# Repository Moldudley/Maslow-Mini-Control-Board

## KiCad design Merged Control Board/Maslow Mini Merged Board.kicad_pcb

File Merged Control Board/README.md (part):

# Maslow Mini — Merged Control Board

A third KiCad project that puts both existing boards on one PCB:

| Source | What it is | Files |
|---|---|---|
| `../Motor Controller Board/` | "Four Motor Control Board M5" — ESP32-S3, 4× DRV8876 belt-axis drivers, TCA9546A I²C mux, SD NAND, LM2596 3.3 V buck, XT60 inlet | **PCB only, no schematic** |
| `../KiCad Boards/` | "Driver Board 2026-08-01" — ESP32-S3, 2× MP6541A 3-phase drivers, MP2459 3.3 V buck, beam-break homing, vacuum control | schematic + PCB |

**Scope: schematic, plus a partially-placed PCB.** The mechanically-constrained parts are placed;
the rest are staged off-board for manual placement. Nothing is routed yet.

The merge is in two parts: joining the two circuits, and then removing the redundancy that a
single board makes pointless. **169 parts / 61 BOM lines → 156 parts / 53 BOM lines.**

## The design decision you asked for

Both ESP32-S3 MCUs are retained. They are wired to each other **only** on the BoardCom pair,
which is exactly what the mated `H1` 2×5 headers used to carry:

| Merged net | Motor section | Driver section |
|---|---|---|
| `BOARDCOM_A` | `U110` pin 9 — IO16 | `U12` pin 31 — IO38 |
| `BOARDCOM_B` | `U110` pin 8 — IO15 | `U12` pin 32 — IO39 |

Note the crossover. On the original boards both headers carried a net called `BOARDCOM1` on
pins 1/3 and `BOARDCOM2` on pins 2/4 — but with the *opposite* assignment on each board, so
mating them swapped the pair. That swap is preserved here.

`H1` is deleted from both sections. Its remaining pins were power, so:

* pins 6/8/10 (`VIN` on the driver, `VCC` on the motor board) become **one shared `VIN` rail**
* pins 5/7/9 become **one shared `GND`**

## What was consolidated

Once both circuits sit on one board, some parts are doing the same job twice.

### One 3.3 V regulator

The driver board's `U2` was an **MP2459 — 0.5 A**, feeding an ESP32-S3-WROOM-1 that peaks around
355 mA on WiFi transmit. That rail had almost no margin before the merge. The motor board's
`U116` is an **LM2596-3.3 — 3 A**. Combined 3.3 V load across both sections is roughly 530 mA
typical, ~950 mA worst case, so the LM2596 carries both with ~3× headroom.

Deleted: `U2`, `L3` (47 µH), `D2` (catch), `D6` (OR-ing), `C80`, `C81`, `R61`, `R62`, `R63`.
`D7` is kept and now ORs the driver USB port's VBUS into the shared `VIN_BUCK`, so either USB
port can still power the whole board. `+3V3_MC` and `+3V3_DRV` are gone; there is one `+3V3`.

### One reset

The motor MCU had no reset button at all — just an RC on `EN`. Both `EN` pins now share one net
(`RST`) driven by `SW2`, with `R28` (10 kΩ) and `C134` (1 µF) as the single RC. `R128` and `C30`
are deleted. The 1 µF is kept over the driver board's 100 nF because that is the value
Espressif's design guide asks for.

### One power-on LED, one Schottky part number

`D101` + `R115` deleted; the driver section's `LED2` + `R17` is kept (3.6 mA rather than 11 mA,
and the LED was explicitly specified for low forward voltage on a 3.3 V rail). `D102`/`D103`
change from SS14 (40 V / 1 A) to the SS36 (60 V / 3 A) already used by `D7` — one BOM line
instead of two, and more margin on a 24 V rail that also carries six motor stages.

### Summary

| | parts | BOM lines |
|---|---|---|
| MP2459 buck chain | 9 | 6 |
| second power-on LED | 2 | 1 |
| second EN RC | 2 | 0 |
| SS14 → SS36 | 0 | 1 |
| **total** | **13** | **8** |

Nothing was added.

## What stays separate

Each section keeps its own ESP32-S3, its own USB-C programming port and its own boot button
(`BOOT_MC` / `BOOT_DRV`). Combining the two MCUs was explicitly out of scope. Combining the two
USB ports would need a hub IC — a net part *increase* — or flashing the driver MCU through the
motor MCU, which costs firmware work and makes recovery from a bad flash harder.

Also deliberately untouched: the VIN bulk capacitance. `C140` (680 µF) and `C72`/`C73`
(2× 220 µF) were sized as two independent reservoirs because a header sat between them, and one
of the 220 µF is probably surplus now — but that is a ripple-current question, not a schematic
one. The ten 1 kΩ I2C pull-ups are also unchanged; each mux channel needs its own pair, though
1 kΩ is unusually strong (2.2–4.7 kΩ is conventional).

## Two consequences of running one regulator

1. **USB-only power is tighter.** Each buck used to have its own port's 500 mA. Now both MCUs
   run from whichever single port is plugged in — fine for flashing (~230 mA from 5 V), close to
   the limit with both radios live (~460 mA). Plugging in both ports does not help; the diode-OR
   takes only the higher one.
2. **Dropout on USB power.** The LM2596 needs roughly Vout + 1.5–2 V. 5 V minus cable sag minus
   the OR-ing diode leaves ~4.3 V at high load. Fine at flashing currents, marginal at full load.
   This already existed on the motor board; merging just makes more depend on it.

## Naming

| Original | Merged | Why |
|---|---|---|
| motor `VCC` | `VIN` | merges with the driver rail H1 used to carry |
| motor `3V3`, driver `3V3` | `+3V3` | one regulator now, so one rail |
| motor `MCU_RST`, driver `RST` | `RST` | one reset for both MCUs |
| motor `U16_1`, driver `VIN_BUCK` | `VIN_BUCK` | one buck input, fed by three OR-ing diodes |
| motor `BOOT` | `BOOT_MC` | each MCU keeps its own boot button |
| driver `BOOT` | `BOOT_DRV` | " |
| motor `L2_1`, `U2_6`… | `SW_BUCK`, `IPROPI_TR`… | the source PCB had auto-generated net names |

Motor-section reference designators are **the originals + 100** (`U2`→`U102`, `C7`→`C107`,
`CN3`→`CN103`, …). The driver section keeps its own designators unchanged; its highest was
`C82`, so nothing collides and you can still map any part back to its source board.

## Files

```
Maslow Mini Merged Board.kicad_pro    project
Maslow Mini Merged Board.kicad_sch    root sheet — the two sections + the BoardCom link
Maslow Mini Merged Board.kicad_pcb    board — 20 parts placed, 136 staged, nothing routed
motor_control_section.kicad_sch       page 2
driver_section.kicad_sch              page 3
MaslowMerged.kicad_sym                symbols authored for the motor-control parts
MaslowMerged.pretty/                  footprints extracted from the motor board's PCB
ProPrj_Dri-easyedapro.kicad_sym       symbols carried over from the driver board
ProPrj_Dri-easyedapro.pretty/         footprints carried over from the driver board
tools/                                the scripts that generated all of the above
```

## PCB layout

`tools/pcb_layout.py` builds the board. **20 parts keep the exact position they had on their
own board** — every motor driver IC and every connector:

| | parts |
|---|---|
| motor drivers | `U102` `U103` `U105` `U106` (DRV8876), `U14` `U15` (MP6541A) |
| power / data | `U101` (XT60), `USB102`, `USB1` |
| motor outputs | `CN101` `CN103` `CN104` `CN110`, `CN3` `CN4` |
| axis encoders | `CN105` `CN109` `CN111` `CN112` |
| vacuum | `CN5` |

Each section keeps its internal geometry exactly. The motor section sits at its original
coordinates; the **driver section is translated as a rigid body by (+71.5, −4.5) mm** so the two
sit side by side with a 5 mm gap and their tops aligned. Board side and rotation are preserved
for every part — the driver section's ICs and connectors are on `B.Cu`, as they were.

The remaining 136 parts are staged to the right of the board in two labelled groups, one per
section, sorted by reference, each keeping its original rotation and board side.

Footprint instances are lifted **verbatim** out of the two source PCBs, so pad shapes, back-side
mirroring, custom padstacks and 3D model references all survive; only position, reference, net
names and the schematic path are rewritten. The two exceptions are `D102`/`D103`, whose footprint
changed with the SS14 → SS36 swap; those are built fresh from `Diode_SMD:D_SMA`.

### The board outline is a placeholder

`Edge.Cuts` is a plain 143 × 115 mm rectangle. Both original board outlines — including their
internal cutouts, which are clearly mechanical — are drawn on `Dwgs.User` so you can see exactly
where each board sat and build the real outline from them.

### Not placed, but arguably should be

`IR1` and `CGQ1` are the beam-break homing pair; their positions are as mechanically constrained
as any connector, but they are not connectors and not motor drivers, so they went to staging. Say
the word and they move to their original spots too. The indicator LEDs (`LED102`, `LED103`,
`LED2`) are in the same category if the enclosure has light pipes.

## How each section was produced

**Driver section** is the original schematic file, edited in place — same symbols, same
placement, same graphics for everything that survives. The edits are: delete the listed symbols,
convert the two surviving BoardCom labels to hierarchical pins, rename `3V3`/`BOOT`, and retarget
the instance paths at this project. Everything the deletions leave behind — labels that sat on a
deleted pin, wires with nothing at one end, junctions in a wholly removed branch — is found by
walking the sheet's connectivity graph rather than by hard-coded position, so the script stays
correct if the source schematic moves. Two cosmetic repairs come with that: `D7`'s reference and
value text had been parked at `D2`'s position by whoever added those diodes, and was re-seated
next to `D7` once `D2` went; and the block captioned "3.3V Regulator / 200ma LDO / Power OR-ing
with PMOS" — describing an arrangement this schematic never actually contained — is retitled
"3.3 V DECOUPLING" with the stale notes removed.

**Motor control section** had to be reconstructed: that board exists only as a PCB. Its
connectivity here is taken pin-for-pin from `Four Motor Control Board M5_*.kicad_pcb`, and its
symbols were authored from the datasheet pinouts, each one cross-checked against how the PCB
actually wires the part (e.g. the 100 nF from DRV8876 pin 12 to VM identifies pin 12 as VCP,
which fixes the whole right-hand side of that package). Connectivity is drawn with a label on
every pin rather than routed wires — the same style the driver board's own EasyEDA-imported
schematic uses.

## Verification

`tools/verify_netlist.py` compares the merged schematic's netlist against both source boards
as a *partition of pins*, so net naming is irrelevant — what must match is which pins end up
electrically common. Every intentional change is declared in that script and applied to the
expectation, so anything else that moved would show up as a mismatch. Current result:

```
declared deletions: 15 parts
expected multi-pin nets: 124   actual: 124
EXACT MATCH - every remaining source net is reproduced, and nothing beyond the
declared changes was altered.
```

The thirteen pins the merged schematic carries that the sources do not are pads that were
simply unconnected on the source PCB and are now explicit: `SW101` 1/3, `U109` 1/7 (SD NAND
DAT1/DAT2, unused in SPI mode), `USB102` A8/B8 (SBU), and seven spare ESP32 IOs on `U110`.

`tools/verify_pcb.py` then checks the board against the schematic: every component present
exactly once with the right footprint, every pad carrying the net the schematic gives it
(compared as a partition again), every footprint's schematic path pointing at the right sheet and
symbol, and every part that was supposed to keep its position sitting exactly where it was to
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
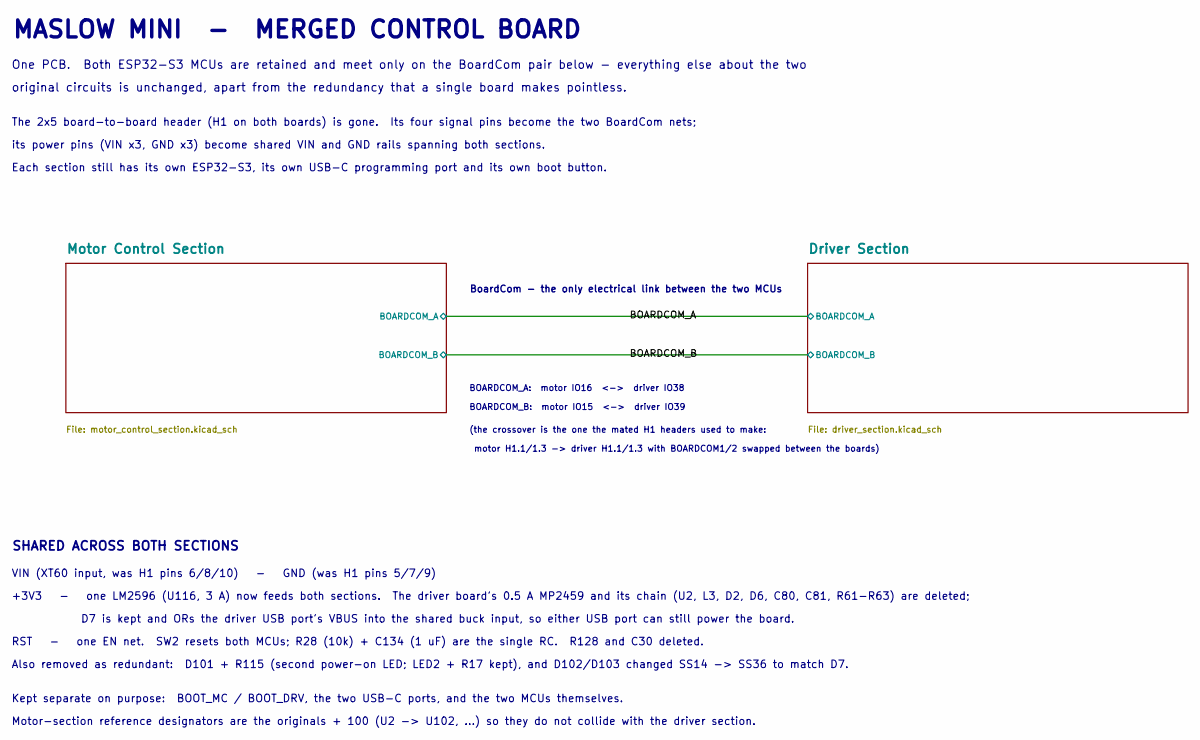
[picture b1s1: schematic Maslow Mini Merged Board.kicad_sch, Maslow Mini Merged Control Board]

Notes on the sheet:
MASLOW MINI - MERGED CONTROL BOARD
One PCB. Both ESP32-S3 MCUs are retained and meet only on the BoardCom pair below - everything else about the two
original circuits is unchanged, apart from the redundancy that a single board makes pointless.
The 2x5 board-to-board header (H1 on both boards) is gone. Its four signal pins become the two BoardCom nets;
its power pins (VIN x3, GND x3) become shared VIN and GND rails spanning both sections.
Each section still has its own ESP32-S3, its own USB-C programming port and its own boot button.
BoardCom - the only electrical link between the two MCUs
BOARDCOM_A: motor IO16 <-> driver IO38
BOARDCOM_B: motor IO15 <-> driver IO39
(the crossover is the one the mated H1 headers used to make:
motor H1.1/1.3 -> driver H1.1/1.3 with BOARDCOM1/2 swapped between the boards)
SHARED ACROSS BOTH SECTIONS
VIN (XT60 input, was H1 pins 6/8/10) - GND (was H1 pins 5/7/9)
+3V3 - one LM2596 (U116, 3 A) now feeds both sections. The driver board's 0.5 A MP2459 and its chain (U2, L3, D2, D6, C80, C81, R61-R63) are deleted;
D7 is kept and ORs the driver USB port's VBUS into the shared buck input, so either USB port can still power the board.
RST - one EN net. SW2 resets both MCUs; R28 (10k) + C134 (1 uF) are the single RC. R128 and C30 deleted.
Also removed as redundant: D101 + R115 (second power-on LED; LED2 + R17 kept), and D102/D103 changed SS14 -> SS36 to match D7.
Kept separate on purpose: BOOT_MC / BOOT_DRV, the two USB-C ports, and the two MCUs themselves.
Motor-section reference designators are the originals + 100 (U2 -> U102, ...) so they do not collide with the driver section.

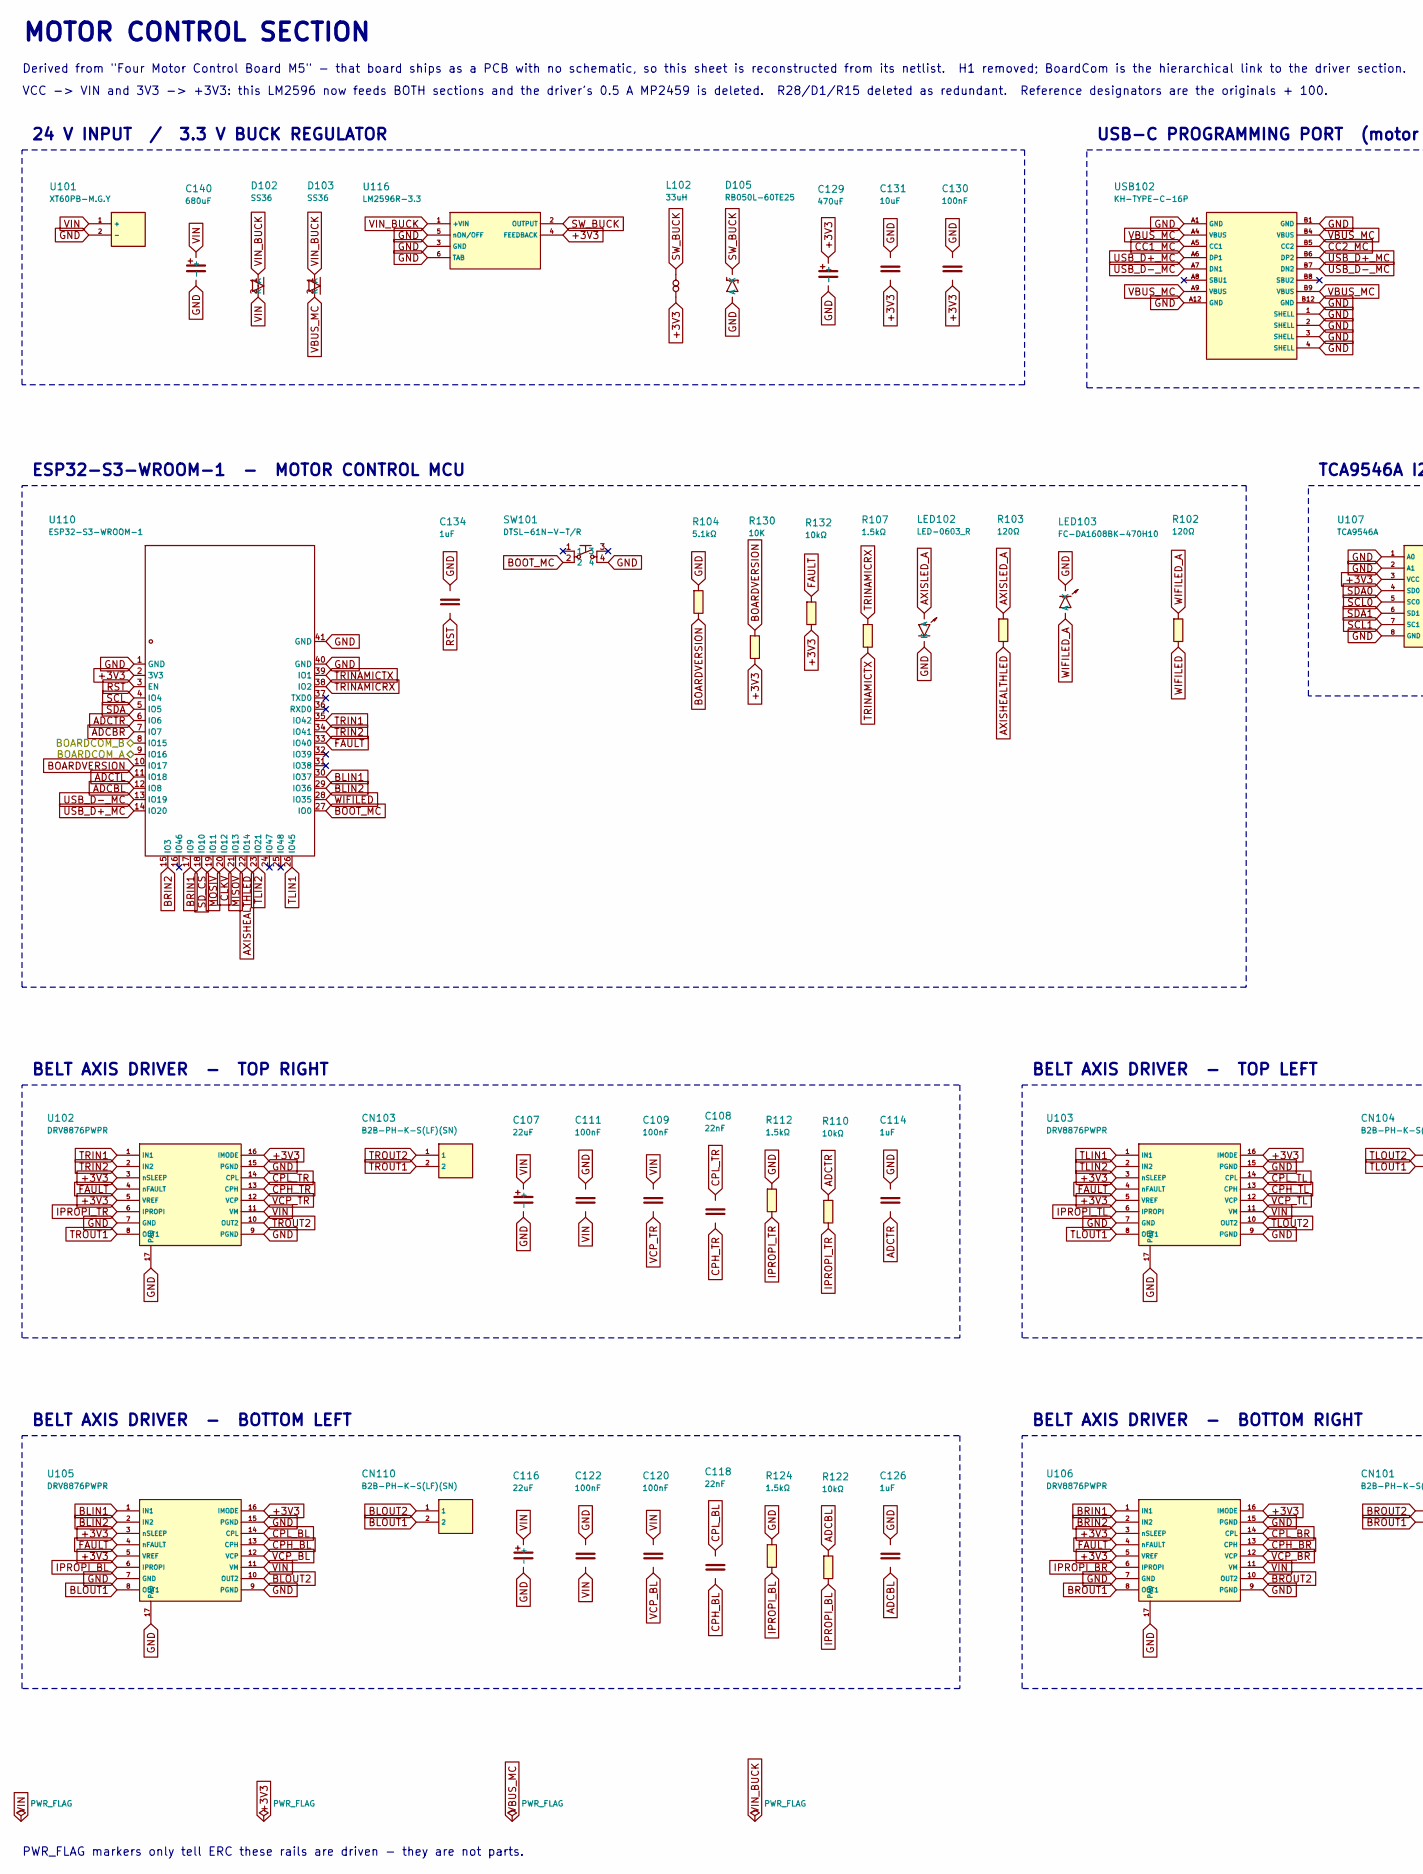
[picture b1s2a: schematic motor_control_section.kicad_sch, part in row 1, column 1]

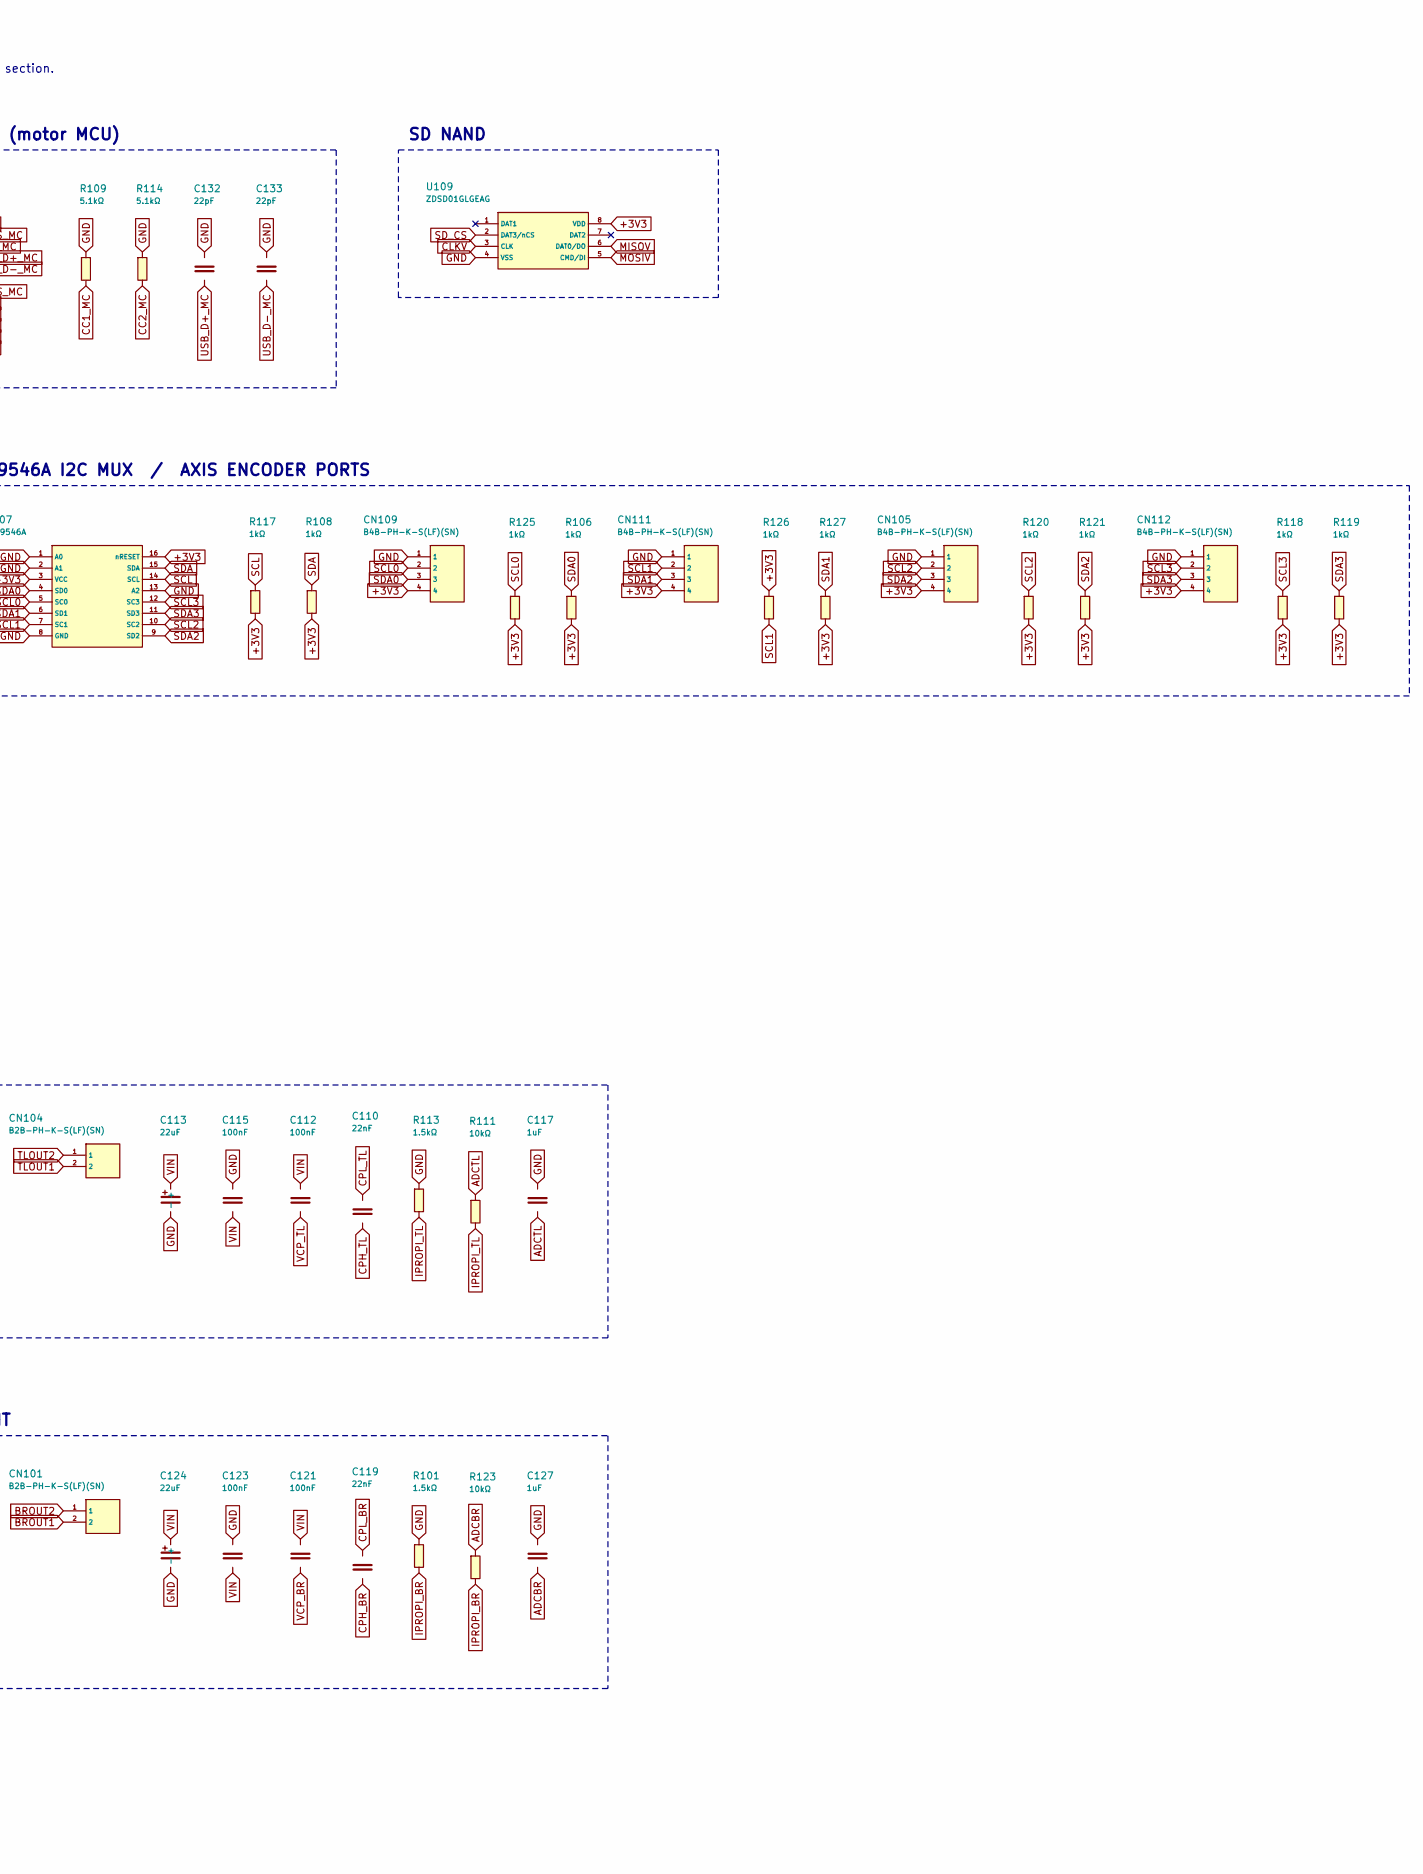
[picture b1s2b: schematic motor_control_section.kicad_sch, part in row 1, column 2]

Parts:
C107, C113, C116, C124: 22uF; CAP-SMD_BD6.3-L6.6-W6.6-LS7.3-FD
C108, C110, C118, C119: 22nF; C0805
C109, C111, C112, C115, C120, C121, C122, C123: 100nF; C0805
C114, C117, C126, C127: 1uF; C0805
C129: 470uF; CAP-SMD_BD6.3-L6.6-W6.6-LS7.6-RD
C130: 100nF; C0603
C131: 10uF; C0805
C132, C133: 22pF; C0603
C134: 1uF; C0603
C140: 680uF; CAP-SMD_BD10.0-L10.3-W10.3-LS10.9-FD
CN101, CN103, CN104, CN110: B2B-PH-K-S(LF)(SN); CONN-TH_B2B-PH-K-S
CN105, CN109, CN111, CN112: B4B-PH-K-S(LF)(SN); CONN-TH_B4B-PH-K-S
D102, D103: SS36; D_SMA
D105: RB050L-60TE25; SMA_L4.3-W2.7-LS5.1-RD
L102: 33uH; IND-SMD_L6.0-W6.0
LED102: LED-0603_R; LED0603_RED
LED103: FC-DA1608BK-470H10; LED0603-RD
R101, R107, R112, R113, R124: 1.5kΩ; R0805
R102, R103: 120Ω; R0603
R104, R109, R114: 5.1kΩ; R0805
R106, R108, R117, R118, R119, R120, R121, R125, R126, R127: 1kΩ; R0402
R110, R111, R122, R123, R132: 10kΩ; R0805
R130: 10K; R0603
SW101: DTSL-61N-V-T/R; SW-SMD_4P-L6.2-W6.4-P4.00-LS7.2
U101: XT60PB-M.G.Y; CONN-TH_XT60PB-M
U102, U103, U105, U106: DRV8876PWPR; HTSSOP-16_L5.0-W4.4-P0.65-LS6.4-BL-EP
U107: TCA9546A; SOP-16_L5.0-W4.4-P0.65-LS6.4-BL
U109: ZDSD01GLGEAG; LGA-8_L6.0-W8.0-P1.27-BL
U110: ESP32-S3-WROOM-1; WIRELM-SMD_ESP32-S3-WROOM-1
U116: LM2596R-3.3; TO-263-5_L10.2-W8.6-P1.70-LS14.4-TL
USB102: KH-TYPE-C-16P; USB-C-SMD_KH-TYPE-C-16P

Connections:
+3V3: C129.1 (+), C130.2, C131.2, CN105.4, CN109.4, CN111.4, CN112.4, L102.2, R106.2, R108.2, R117.2, R118.2, R119.2, R120.2, R121.2, R125.2, R126.1, R127.2, R130.2, R132.2, U102.3 (nSLEEP), U102.5 (VREF), U102.16 (IMODE), U103.3 (nSLEEP), U103.5 (VREF), U103.16 (IMODE), U105.3 (nSLEEP), U105.5 (VREF), U105.16 (IMODE), U106.3 (nSLEEP), U106.5 (VREF), U106.16 (IMODE), U107.3 (VCC), U107.16 (nRESET), U109.8 (VDD), U110.2 (3V3), U116.4 (FEEDBACK); also elsewhere on the board
/BOARDCOM_A: U110.9 (IO16); also elsewhere on the board
/BOARDCOM_B: U110.8 (IO15); also elsewhere on the board
ADCBL: C126.2, R122.1, U110.12 (IO8)
ADCBR: C127.2, R123.1, U110.7 (IO7)
ADCTL: C117.2, R111.1, U110.11 (IO18)
ADCTR: C114.2, R110.1, U110.6 (IO6)
AXISHEALTHLED: R103.2, U110.22 (IO14)
AXISLED_A: LED102.1 (A), R103.1
BLIN1: U105.1 (IN1), U110.30 (IO37)
BLIN2: U105.2 (IN2), U110.29 (IO36)
BLOUT1: CN110.2, U105.8 (OUT1)
BLOUT2: CN110.1, U105.10 (OUT2)
BOARDVERSION: R104.2, R130.1, U110.10 (IO17)
BOOT_MC: SW101.2, U110.27 (IO0)
BRIN1: U106.1 (IN1), U110.17 (IO9)
BRIN2: U106.2 (IN2), U110.15 (IO3)
BROUT1: CN101.2, U106.8 (OUT1)
BROUT2: CN101.1, U106.10 (OUT2)
CC1_MC: R109.2, USB102.A5 (CC1)
CC2_MC: R114.2, USB102.B5 (CC2)
CLKV: U109.3 (CLK), U110.20 (IO12)
CPH_BL: C118.2, U105.13 (CPH)
CPH_BR: C119.2, U106.13 (CPH)
CPH_TL: C110.2, U103.13 (CPH)
CPH_TR: C108.2, U102.13 (CPH)
CPL_BL: C118.1, U105.14 (CPL)
CPL_BR: C119.1, U106.14 (CPL)
CPL_TL: C110.1, U103.14 (CPL)
CPL_TR: C108.1, U102.14 (CPL)
FAULT: R132.1, U102.4 (nFAULT), U103.4 (nFAULT), U105.4 (nFAULT), U106.4 (nFAULT), U110.33 (IO40)
GND: C107.2 (-), C111.1, C113.2 (-), C114.1, C115.1, C116.2 (-), C117.1, C122.1, C123.1, C124.2 (-), C126.1, C127.1, C129.2 (-), C130.1, C131.1, C132.1, C133.1, C134.1, C140.2 (-), CN105.1, CN109.1, CN111.1, CN112.1, D105.2 (A), LED102.2 (K), LED103.1 (K), R101.1, R104.1, R109.1, R112.1, R113.1, R114.1, R124.1, SW101.4, U101.2 (-), U102.7 (GND), U102.9 (PGND), U102.15 (PGND), U102.17 (PAD), U103.7 (GND), U103.9 (PGND), U103.15 (PGND), U103.17 (PAD), U105.7 (GND), U105.9 (PGND), U105.15 (PGND), U105.17 (PAD), U106.7 (GND), U106.9 (PGND), U106.15 (PGND), U106.17 (PAD), U107.1 (A0), U107.2 (A1), U107.8 (GND), U107.13 (A2), U109.4 (VSS), U110.1 (GND), U110.40 (GND), U110.41 (GND), U116.3 (GND), U116.5 (nON/OFF), U116.6 (TAB), USB102.1 (SHELL), USB102.2 (SHELL), USB102.3 (SHELL), USB102.4 (SHELL), USB102.A1 (GND), USB102.A12 (GND), USB102.B1 (GND), USB102.B12 (GND); also elsewhere on the board
IPROPI_BL: R122.2, R124.2, U105.6 (IPROPI)
IPROPI_BR: R101.2, R123.2, U106.6 (IPROPI)
IPROPI_TL: R111.2, R113.2, U103.6 (IPROPI)
IPROPI_TR: R110.2, R112.2, U102.6 (IPROPI)
MISOV: U109.6 (DAT0/DO), U110.21 (IO13)
MOSIV: U109.5 (CMD/DI), U110.19 (IO11)
RST: C134.2, U110.3 (EN); also elsewhere on the board
SCL: R117.1, U107.14 (SCL), U110.4 (IO4)
SCL0: CN109.2, R125.1, U107.5 (SC0)
SCL1: CN111.2, R126.2, U107.7 (SC1)
SCL2: CN105.2, R120.1, U107.10 (SC2)
SCL3: CN112.2, R118.1, U107.12 (SC3)
SDA: R108.1, U107.15 (SDA), U110.5 (IO5)
SDA0: CN109.3, R106.1, U107.4 (SD0)
SDA1: CN111.3, R127.1, U107.6 (SD1)
SDA2: CN105.3, R121.1, U107.9 (SD2)
SDA3: CN112.3, R119.1, U107.11 (SD3)
SD_CS: U109.2 (DAT3/nCS), U110.18 (IO10)
SW_BUCK: D105.1 (K), L102.1, U116.2 (OUTPUT)
TLIN1: U103.1 (IN1), U110.26 (IO45)
TLIN2: U103.2 (IN2), U110.23 (IO21)
TLOUT1: CN104.2, U103.8 (OUT1)
TLOUT2: CN104.1, U103.10 (OUT2)
TRIN1: U102.1 (IN1), U110.35 (IO42)
TRIN2: U102.2 (IN2), U110.34 (IO41)
TRINAMICRX: R107.1, U110.38 (IO2)
TRINAMICTX: R107.2, U110.39 (IO1)
TROUT1: CN103.2, U102.8 (OUT1)
TROUT2: CN103.1, U102.10 (OUT2)
USB_D+_MC: C132.2, U110.14 (IO20), USB102.A6 (DP1), USB102.B6 (DP2)
USB_D-_MC: C133.2, U110.13 (IO19), USB102.A7 (DN1), USB102.B7 (DN2)
VBUS_MC: D103.2 (A), USB102.A4 (VBUS), USB102.A9 (VBUS), USB102.B4 (VBUS), USB102.B9 (VBUS)
VCP_BL: C120.2, U105.12 (VCP)
VCP_BR: C121.2, U106.12 (VCP)
VCP_TL: C112.2, U103.12 (VCP)
VCP_TR: C109.2, U102.12 (VCP)
VIN: C107.1 (+), C109.1, C111.2, C112.1, C113.1 (+), C115.2, C116.1 (+), C120.1, C121.1, C122.2, C123.2, C124.1 (+), C140.1 (+), D102.2 (A), U101.1 (+), U102.11 (VM), U103.11 (VM), U105.11 (VM), U106.11 (VM); also elsewhere on the board
VIN_BUCK: D102.1 (K), D103.1 (K), U116.1 (+VIN); also elsewhere on the board
WIFILED: R102.2, U110.28 (IO35)
WIFILED_A: LED103.2 (A), R102.1

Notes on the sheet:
MOTOR CONTROL SECTION
Derived from "Four Motor Control Board M5" - that board ships as a PCB with no schematic, so this sheet is reconstructed from its netlist. H1 removed; BoardCom is the hierarchical link to the driver section.
VCC -> VIN and 3V3 -> +3V3: this LM2596 now feeds BOTH sections and the driver's 0.5 A MP2459 is deleted. R28/D1/R15 deleted as redundant. Reference designators are the originals + 100.
24 V INPUT / 3.3 V BUCK REGULATOR
USB-C PROGRAMMING PORT (motor MCU)
SD NAND
ESP32-S3-WROOM-1 - MOTOR CONTROL MCU
TCA9546A I2C MUX / AXIS ENCODER PORTS
BELT AXIS DRIVER - TOP RIGHT
BELT AXIS DRIVER - TOP LEFT
BELT AXIS DRIVER - BOTTOM LEFT
BELT AXIS DRIVER - BOTTOM RIGHT
PWR_FLAG markers only tell ERC these rails are driven - they are not parts.

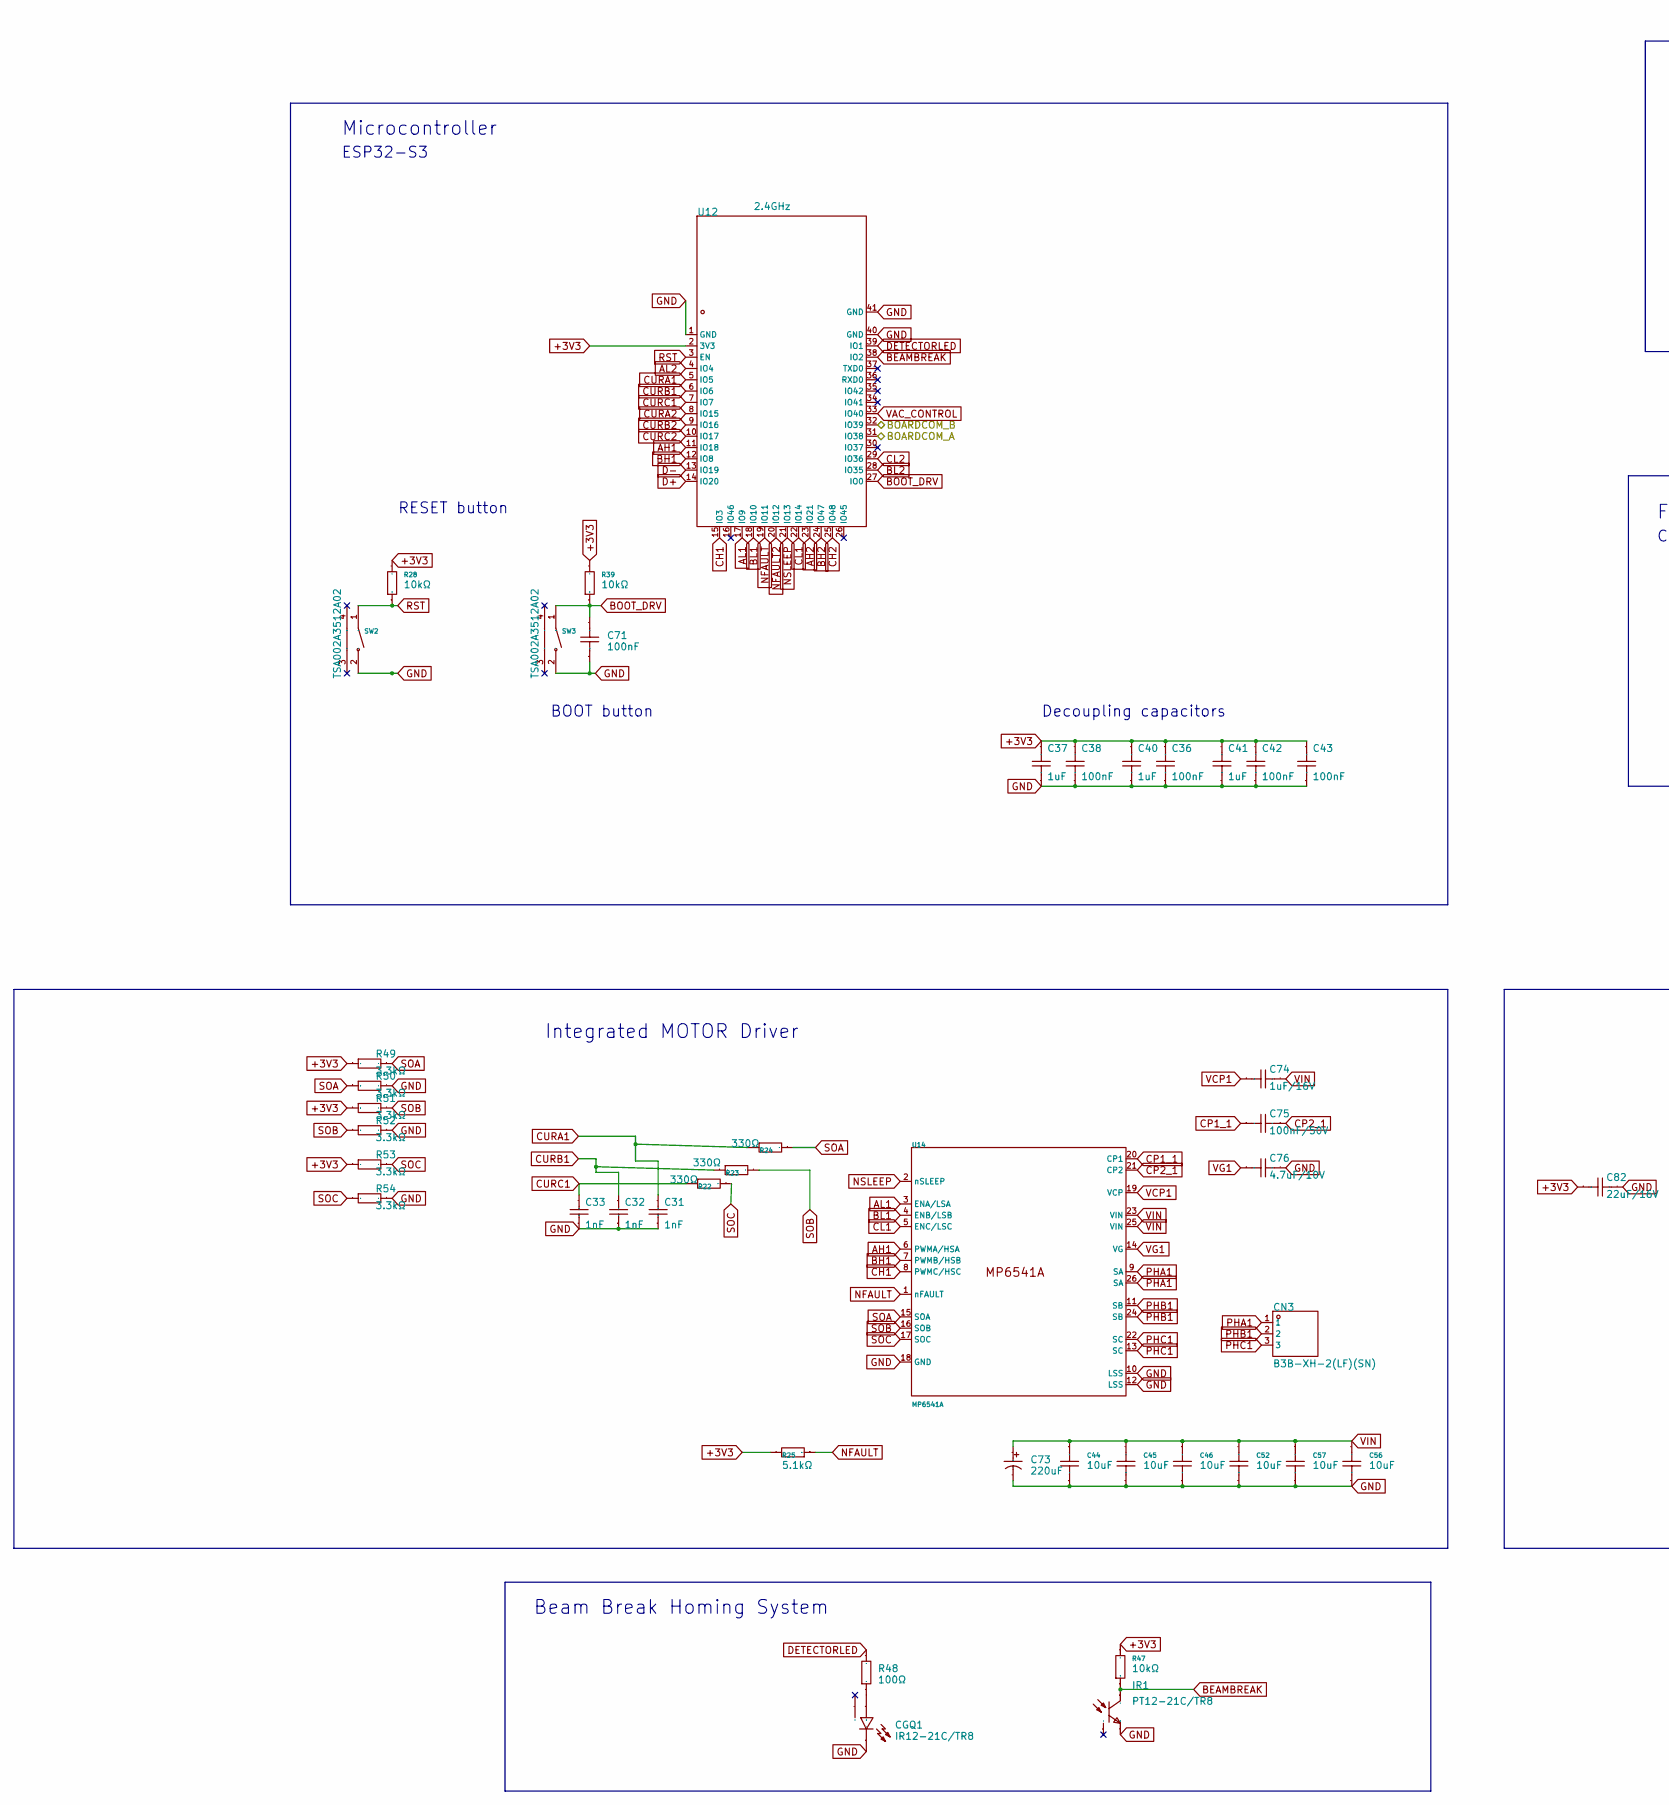
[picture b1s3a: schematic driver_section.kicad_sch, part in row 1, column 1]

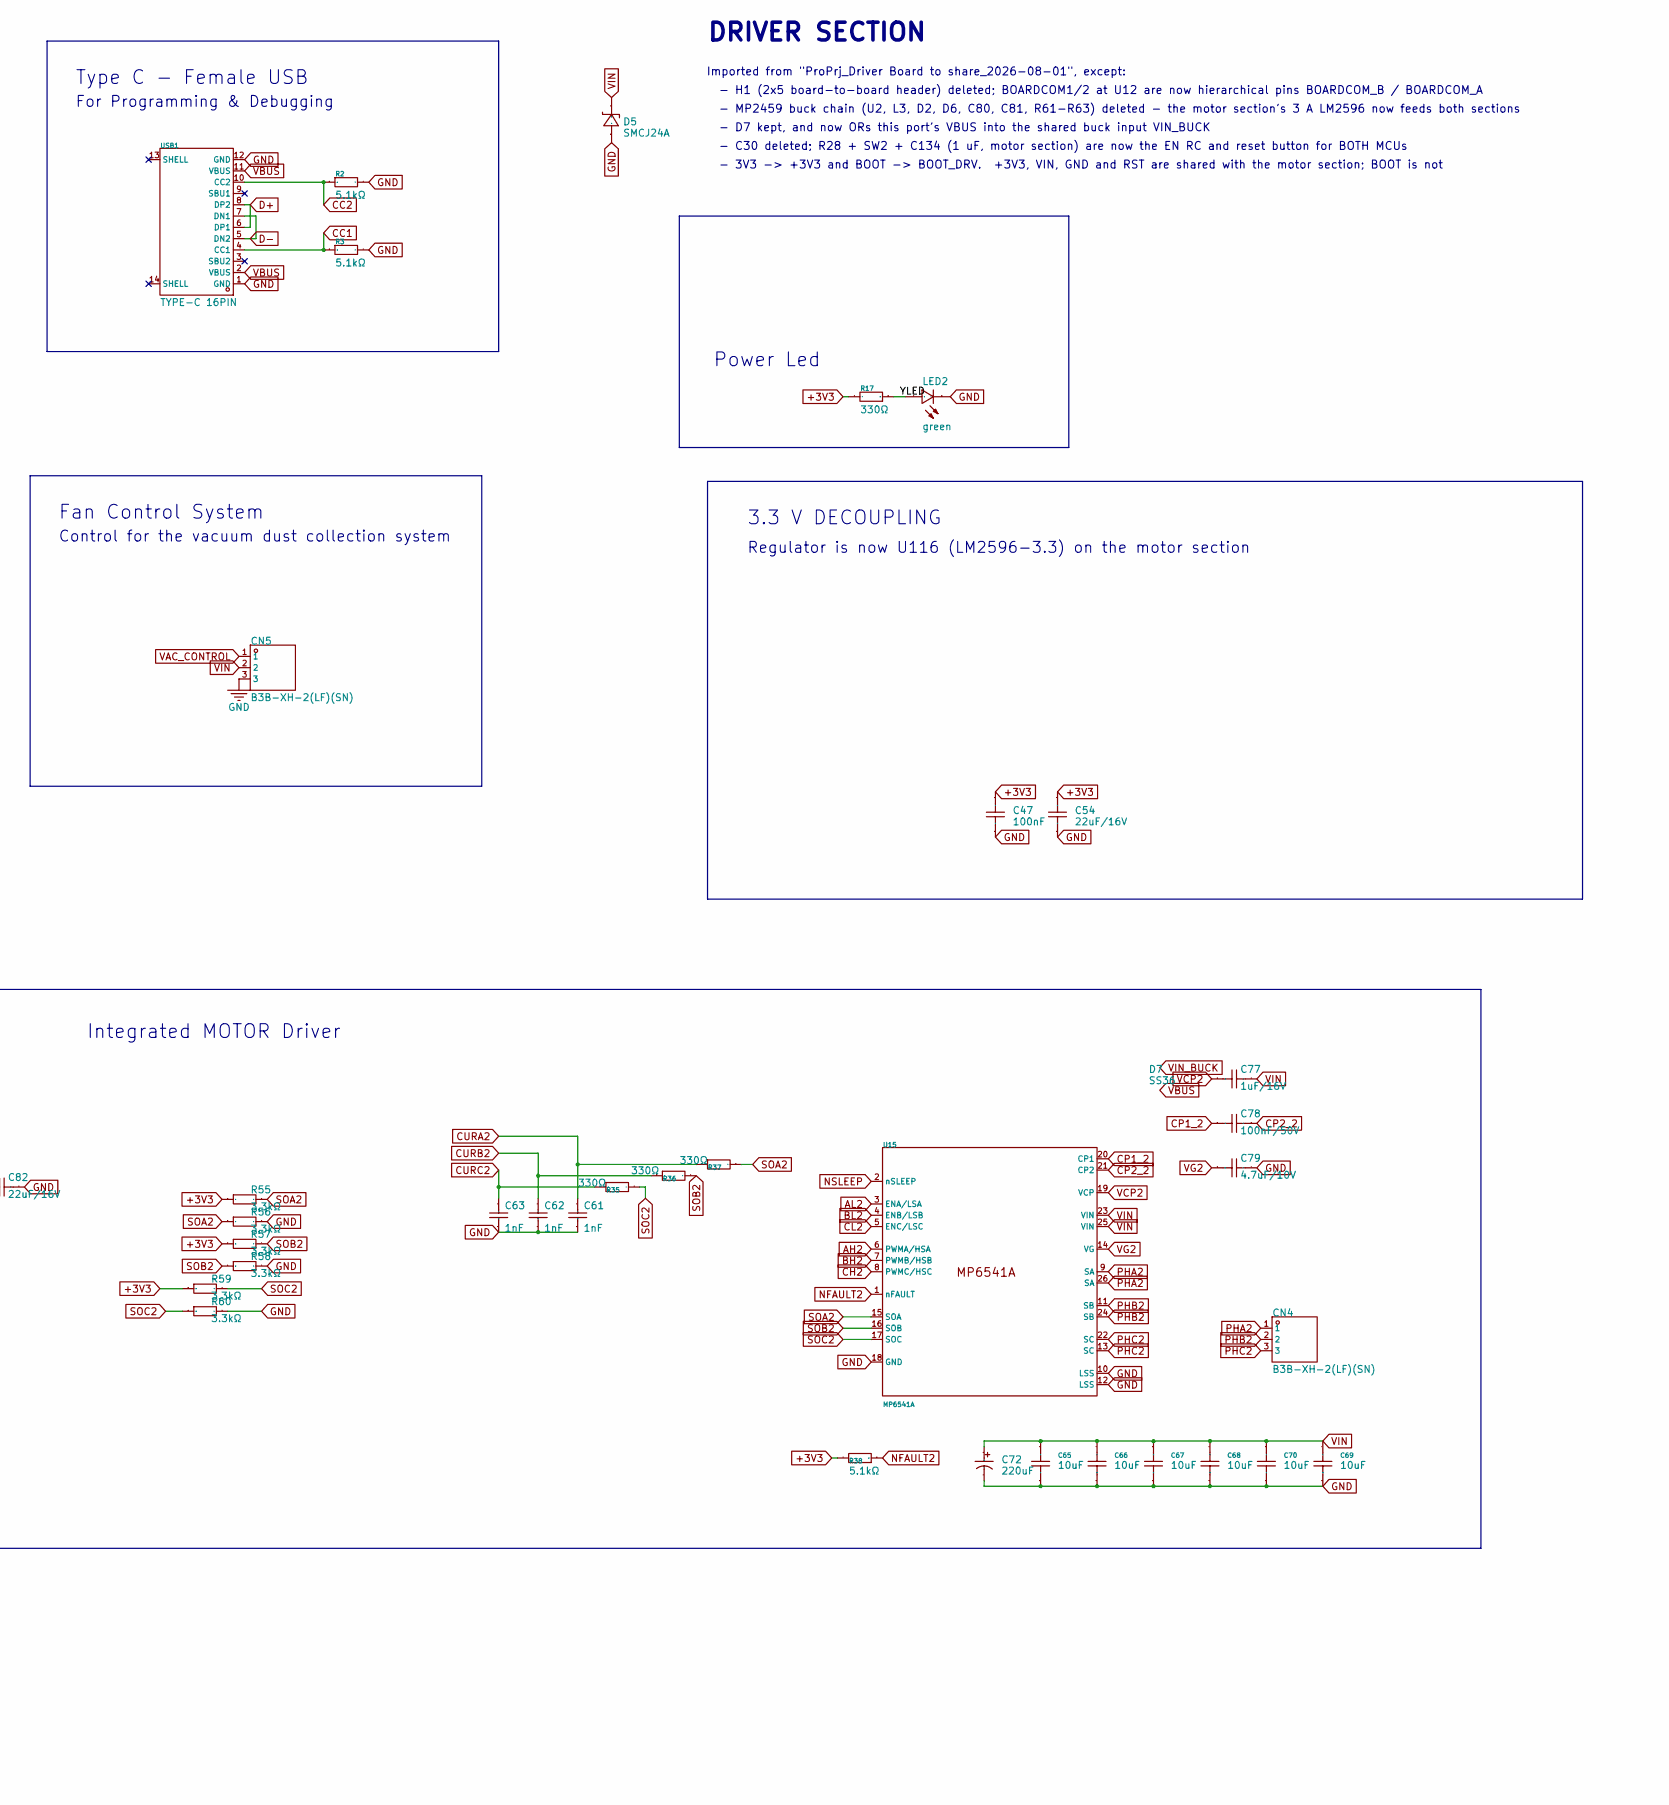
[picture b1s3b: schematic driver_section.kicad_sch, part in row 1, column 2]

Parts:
C31, C32, C33, C61, C62, C63: 1nF; C0402; Manufacturer Part CL05B102KB5NNNC; LCSC Part Name 1nF ±10% 50V X7R 0402 MLCC
C36, C38, C42, C43, C47, C71: 100nF; C0402; Manufacturer Part CL05B104KB54PNC; LCSC Part Name 100nF ±10% 50V
C37, C40, C41: 1uF; C0402; Manufacturer Part CL05A105KA5NQNC; LCSC Part Name 1uF ±10% 25V
C44, C45, C46, C52, C56, C57, C65, C66, C67, C68, C69, C70: 10uF; C0805; Manufacturer Part GRM21BR61H106KE43L; LCSC Part Name 10uF ±10% 50V
C54: 22uF/16V; C0805; Manufacturer Part GRM219R61C226ME15L; LCSC Part Name 22uF ±20% 16V X5R 0805 MLCC
C72, C73: 220uF; CAP-TH_BD8.0-P3.50-D0.6-FD; Manufacturer Part ERS1VM221F12OT; LCSC Part Name 220uF ±20% 35V
C74, C77: 1uF/16V; C0603; Manufacturer Part CL10B105KO8NNNC; LCSC Part Name 1µF ±10% 16V X7R 0603 MLCC
C75, C78: 100nF/50V; C0603; Manufacturer Part CL10B104KB8NNNC; LCSC Part Name 100nF ±10% 50V X7R 0603 MLCC
C76, C79: 4.7uF/10V; C0805; Manufacturer Part EMK212B7475KG-T; LCSC Part Name 4.7µF ±10% 16V X7R 0805 MLCC
C82: 22uF/16V; C0805; Manufacturer Part GRM219R61C226ME15L; LCSC Part Name 22µF ±20% 16V X5R 0805 MLCC
CGQ1: IR12-21C/TR8; LED-SMD_IR12-21C-TR8; Manufacturer Part IR12-21C/TR8; LCSC Part Name 65mA红外发射管
CN3, CN4, CN5: B3B-XH-2(LF)(SN); CONN-TH_B3B-XH-2-LF-SN; Manufacturer Part B3B-XH-2(LF)(SN); LCSC Part Name 1x3P 间距:2.5mm 直插 系列:XH
D5: SMCJ24A; SMC_L7.1-W6.2-LS8.1-R-RD; Manufacturer Part SMCJ24A; LCSC Part Name SMCJ24A
D7: SS36; D_SMA; Manufacturer Part SS36; LCSC Part Name SS36 60V 3A Schottky Diode SMA
IR1: PT12-21C/TR8; SENSOR-SMD_L3.0-W2.0-RD; Manufacturer Part PT12-21C/TR8; LCSC Part Name 940nm的NPN光电三极管
LED2: green; LED0603-RD-YELLOW; Manufacturer Part KT-0603YG; LCSC Part Name Green 570nm 0603 LED, Vf 2.0-2.2V, 30-4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
R2, R3, R25, R38: 5.1kΩ; R0402; Manufacturer Part 0402WGF5101TCE; LCSC Part Name 5.1kΩ ±1% 62.5mW 厚膜电阻
R17: 330Ω; R0402; Manufacturer Part 0402WGF3300TCE; LCSC Part Name 330Ω ±1% 1/16W 0402 Chip Resistor
R22, R23, R24, R35, R36, R37: 330Ω; R0402; Manufacturer Part 0402WGF3300TCE; LCSC Part Name 330Ω ±1% 62.5mW 厚膜电阻
R28, R39, R47: 10kΩ; R0402; Manufacturer Part 0402WGF1002TCE; LCSC Part Name 10kΩ ±1% 62.5mW 厚膜电阻
R48: 100Ω; R0402; Manufacturer Part 0402WGF1000TCE; LCSC Part Name 100Ω ±1% 1/16W 0402 Chip Resistor
R49, R50, R51, R52, R53, R54, R55, R56, R57, R58, R59, R60: 3.3kΩ; R0402; Manufacturer Part RC0402FR-073K3L; LCSC Part Name 3.3kΩ ±1% 1/16W 0402 Chip Resistor
SW2, SW3: TSA002A3512A02; SW-SMD_BZCN_TSA002A35XXX; Manufacturer Part TSA002A3512A02; LCSC Part Name 4.8*2*3.5mm 卧贴 轻触开关
U12: 2.4GHz; WIRELM-SMD_ESP32-S3-WROOM-1; Manufacturer Part ESP32-S3-WROOM-1-N8R2; LCSC Part Name 通用型Wi-Fi+低功耗蓝牙MCU模组
U14, U15: MP6541A; TQFN-26 (6X6MM); Manufacturer Part MP6541A
USB1: TYPE-C 16PIN; USB-C-SMD_TYPE-C-6PIN-2MD-073; Manufacturer Part TYPE-C 16PIN; LCSC Part Name Type-C 母 卧贴

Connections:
+3V3: C36.2, C37.2, C38.2, C40.2, C41.2, C42.2, C43.2, C47.2, C54.2, C82.1, R17.2, R25.2, R28.2, R38.2, R39.2, R47.2, R49.1, R51.1, R53.1, R55.1, R57.1, R59.1, U12.2 (3V3); also elsewhere on the board
/BOARDCOM_A: U12.31 (IO38); also elsewhere on the board
/BOARDCOM_B: U12.32 (IO39); also elsewhere on the board
/Driver Section/YLED: LED2.2 (A), R17.1
AH1: U12.11 (IO18), U14.6 (PWMA/HSA)
AH2: U12.23 (IO21), U15.6 (PWMA/HSA)
AL1: U12.17 (IO9), U14.3 (ENA/LSA)
AL2: U12.4 (IO4), U15.3 (ENA/LSA)
BEAMBREAK: IR1.1 (C), R47.1, U12.38 (IO2)
BH1: U12.12 (IO8), U14.7 (PWMB/HSB)
BH2: U12.24 (IO47), U15.7 (PWMB/HSB)
BL1: U12.18 (IO10), U14.4 (ENB/LSB)
BL2: U12.28 (IO35), U15.4 (ENB/LSB)
BOOT_DRV: C71.2, R39.1, SW3.1, U12.27 (IO0)
CC1: R3.1, USB1.4 (CC1)
CC2: R2.1, USB1.10 (CC2)
CH1: U12.15 (IO3), U14.8 (PWMC/HSC)
CH2: U12.25 (IO48), U15.8 (PWMC/HSC)
CL1: U12.22 (IO14), U14.5 (ENC/LSC)
CL2: U12.29 (IO36), U15.5 (ENC/LSC)
CP1_1: C75.1, U14.20 (CP1)
CP1_2: C78.1, U15.20 (CP1)
CP2_1: C75.2, U14.21 (CP2)
CP2_2: C78.2, U15.21 (CP2)
CURA1: C31.2, R24.1, U12.5 (IO5)
CURA2: C61.2, R37.1, U12.8 (IO15)
CURB1: C32.2, R23.1, U12.6 (IO6)
CURB2: C62.2, R36.1, U12.9 (IO16)
CURC1: C33.2, R22.1, U12.7 (IO7)
CURC2: C63.2, R35.1, U12.10 (IO17)
D+: U12.14 (IO20), USB1.6 (DP1), USB1.8 (DP2)
D-: U12.13 (IO19), USB1.5 (DN2), USB1.7 (DN1)
DETECTORLED: R48.2, U12.39 (IO1)
GND: C31.1, C32.1, C33.1, C36.1, C37.1, C38.1, C40.1, C41.1, C42.1, C43.1, C44.1, C45.1, C46.1, C47.1, C52.1, C54.1, C56.1, C57.1, C61.1, C62.1, C63.1, C65.1, C66.1, C67.1, C68.1, C69.1, C70.1, C71.1, C72.2, C73.2, C76.2, C79.2, C82.2, CGQ1.1 (C), CN5.3, D5.1 (A), IR1.2 (E), LED2.1 (C), R2.2, R3.2, R50.2, R52.2, R54.2, R56.2, R58.2, R60.2, SW2.2, SW3.2, U12.1 (GND), U12.40 (GND), U12.41 (GND), U14.10 (LSS), U14.12 (LSS), U14.18 (GND), U15.10 (LSS), U15.12 (LSS), U15.18 (GND), USB1.1 (GND), USB1.12 (GND); also elsewhere on the board
NFAULT: R25.1, U12.19 (IO11), U14.1 (nFAULT)
NFAULT2: R38.1, U12.20 (IO12), U15.1 (nFAULT)
NSLEEP: U12.21 (IO13), U14.2 (nSLEEP), U15.2 (nSLEEP)
unnamed: CGQ1.2 (A), R48.1
PHA1: CN3.1, U14.9 (SA), U14.26 (SA)
PHA2: CN4.1, U15.9 (SA), U15.26 (SA)
PHB1: CN3.2, U14.11 (SB), U14.24 (SB)
PHB2: CN4.2, U15.11 (SB), U15.24 (SB)
PHC1: CN3.3, U14.13 (SC), U14.22 (SC)
PHC2: CN4.3, U15.13 (SC), U15.22 (SC)
RST: R28.1, SW2.1, U12.3 (EN); also elsewhere on the board
SOA: R24.2, R49.2, R50.1, U14.15 (SOA)
SOA2: R37.2, R55.2, R56.1, U15.15 (SOA)
SOB: R23.2, R51.2, R52.1, U14.16 (SOB)
SOB2: R36.2, R57.2, R58.1, U15.16 (SOB)
SOC: R22.2, R53.2, R54.1, U14.17 (SOC)
SOC2: R35.2, R59.2, R60.1, U15.17 (SOC)
VAC_CONTROL: CN5.1, U12.33 (IO40)
VBUS: D7.2 (A), USB1.2 (VBUS), USB1.11 (VBUS)
VCP1: C74.1, U14.19 (VCP)
VCP2: C77.1, U15.19 (VCP)
VG1: C76.1, U14.14 (VG)
VG2: C79.1, U15.14 (VG)
VIN: C44.2, C45.2, C46.2, C52.2, C56.2, C57.2, C65.2, C66.2, C67.2, C68.2, C69.2, C70.2, C72.1, C73.1, C74.2, C77.2, CN5.2, D5.2 (K), U14.23 (VIN), U14.25 (VIN), U15.23 (VIN), U15.25 (VIN); also elsewhere on the board
VIN_BUCK: D7.1 (K); also elsewhere on the board

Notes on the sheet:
Decoupling capacitors
Microcontroller
Regulator is now U116 (LM2596-3.3) on the motor section
Control for the vacuum dust collection system
Integrated MOTOR Driver
ESP32-S3
BOOT button
Power Led
3.3 V DECOUPLING
RESET button
For Programming & Debugging
Type C - Female USB
Beam Break Homing System
Fan Control System
DRIVER SECTION
Imported from "ProPrj_Driver Board to share_2026-08-01", except:
- H1 (2x5 board-to-board header) deleted; BOARDCOM1/2 at U12 are now hierarchical pins BOARDCOM_B / BOARDCOM_A
- MP2459 buck chain (U2, L3, D2, D6, C80, C81, R61-R63) deleted - the motor section's 3 A LM2596 now feeds both sections
- D7 kept, and now ORs this port's VBUS into the shared buck input VIN_BUCK
- C30 deleted; R28 + SW2 + C134 (1 uF, motor section) are now the EN RC and reset button for BOTH MCUs
- 3V3 -> +3V3 and BOOT -> BOOT_DRV. +3V3, VIN, GND and RST are shared with the motor section; BOOT is not

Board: 4 copper layers, 156 parts (104 on the bottom side), 124 nets, no tracks yet.
